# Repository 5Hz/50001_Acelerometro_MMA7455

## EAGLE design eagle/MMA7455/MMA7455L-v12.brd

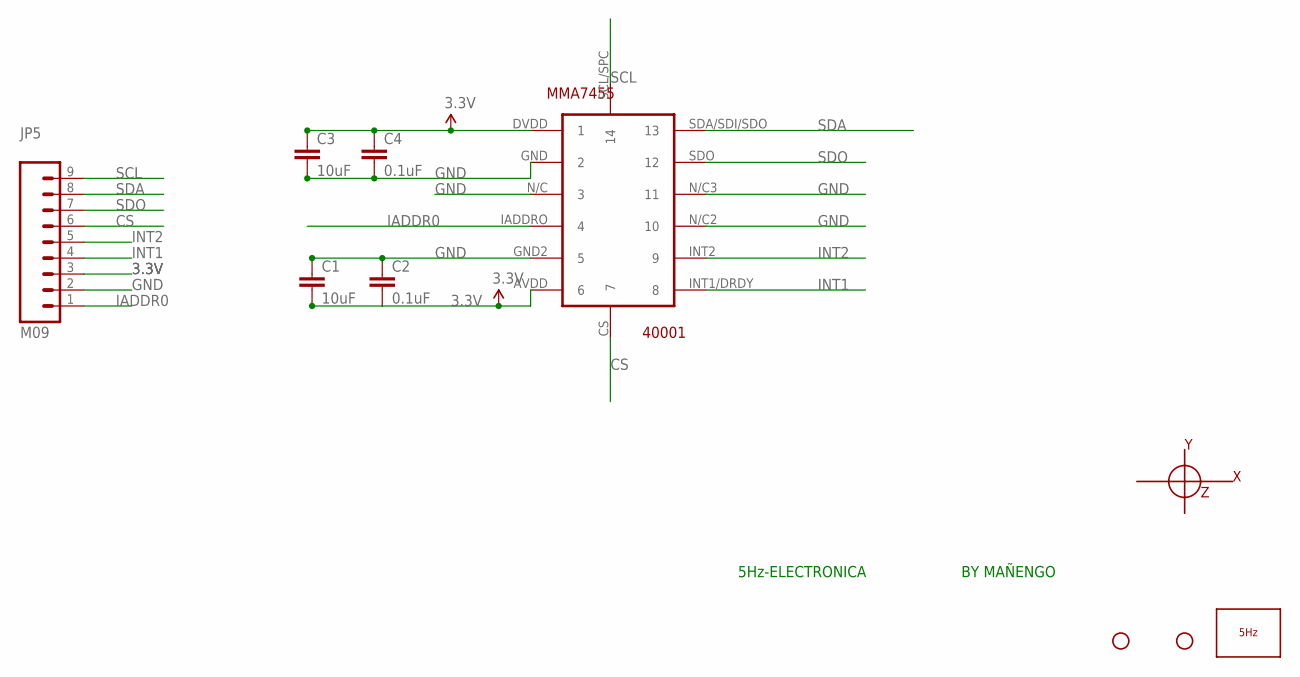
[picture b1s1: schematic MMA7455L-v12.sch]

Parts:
C1, C3: 10uF; 0603-CAP
C2, C4: 0.1uF; 0603-CAP
JP3, JP4: STAND-OFF
JP5: M09; 1X09
LOGO1: LOGO_5HZ_H_10MM; 5HZ_LOGO_H_10MM
MMA7455: 40001; MMA7455L
U$3: EJES_CARTESIANO_5MM; EJE_CARTESIANO_5MM

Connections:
3.3V: C1.2, C2.2, C3.1, C4.1, JP5.3, MMA7455.AVDD (6), MMA7455.DVDD (1)
CS: JP5.6, MMA7455.CS (7)
GND: C1.1, C2.1, C3.2, C4.2, JP5.2, MMA7455.GND (2), MMA7455.GND2 (5), MMA7455.N/C (3), MMA7455.N/C2 (10), MMA7455.N/C3 (11)
IADDR0: JP5.1, MMA7455.IADDRO (4)
INT1: JP5.4, MMA7455.INT1/DRDY (8)
INT2: JP5.5, MMA7455.INT2 (9)
SCL: JP5.9, MMA7455.SCL/SPC (14)
SDA: JP5.8, MMA7455.SDA/SDI/SDO (13)
SDO: JP5.7, MMA7455.SDO (12)

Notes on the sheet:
5Hz-ELECTRONICA
BY MAÑENGO

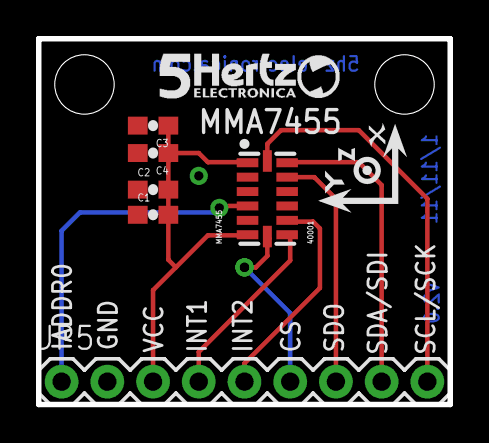
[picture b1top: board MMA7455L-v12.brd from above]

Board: 2 copper layers, 22.9 x 20.3 mm, 10 parts (0 on the bottom side), 9 nets.

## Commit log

2014-01-09 creación
2014-01-09 correción de nombre de carpeta
